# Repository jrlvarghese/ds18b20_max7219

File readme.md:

#DS18B20 is used as a sensor
#MAX7219 used for LED display driver Ic
#Upto 3 digit can be displayed

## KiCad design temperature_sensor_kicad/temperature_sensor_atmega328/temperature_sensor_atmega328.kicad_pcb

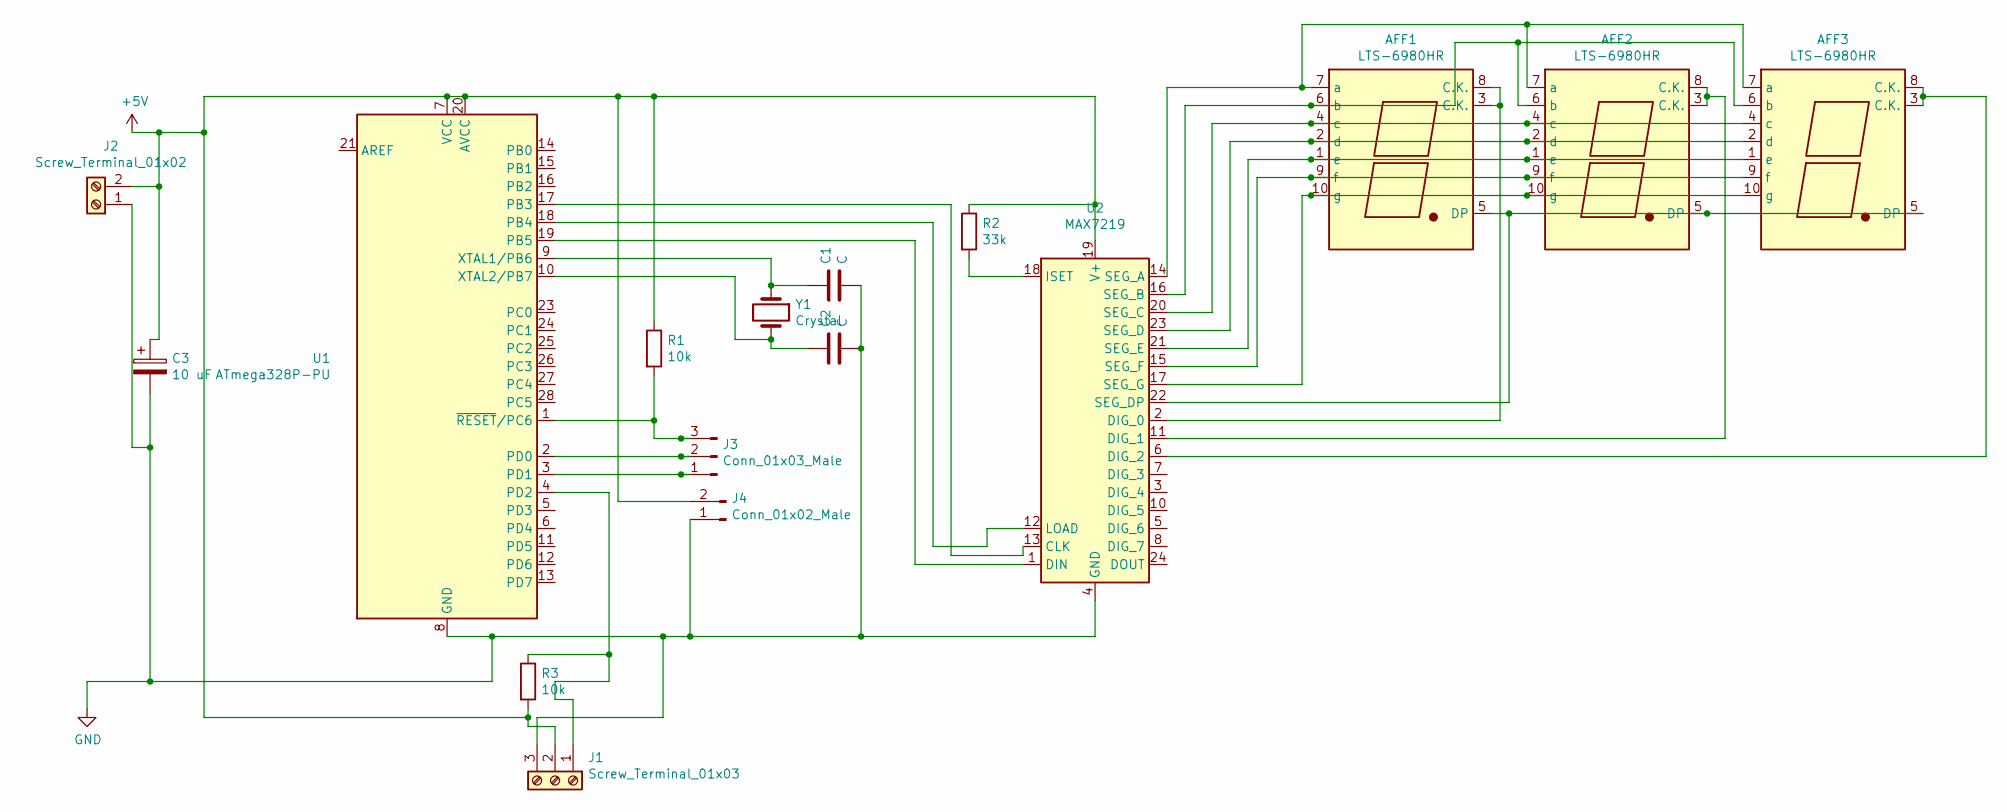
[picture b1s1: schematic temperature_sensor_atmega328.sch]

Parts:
AFF1, AFF2, AFF3: LTS-6980HR; 7SegmentLED_LTS6760_LTS6780
C1, C2: C; C_Disc_D5.0mm_W2.5mm_P5.00mm
C3: 10 uF; CP_Radial_D7.5mm_P2.50mm
J1: Screw_Terminal_01x03; TerminalBlock_bornier-3_P5.08mm
J2: Screw_Terminal_01x02; TerminalBlock_bornier-2_P5.08mm
J3: Conn_01x03_Male; PinHeader_1x03_P2.54mm_Vertical
J4: Conn_01x02_Male; PinHeader_1x02_P2.54mm_Vertical
R1: 10k; R_Axial_DIN0411_L9.9mm_D3.6mm_P15.24mm_Horizontal
R2: 33k; R_Axial_DIN0207_L6.3mm_D2.5mm_P2.54mm_Vertical
R3: 10k; R_Axial_DIN0204_L3.6mm_D1.6mm_P2.54mm_Vertical
U1: ATmega328P-PU; DIP-28_W7.62mm_Socket
U2: MAX7219; DIP-24_W7.62mm
Y1: Crystal; Crystal_HC49-U_Vertical

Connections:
+5V: C3.1, J1.2, J2.2, J4.2, R1.1, R2.1, R3.2, U1.7 (VCC), U1.20 (AVCC), U2.19 (V+)
GND: C1.2, C2.2, C3.2, J1.3, J2.1, J4.1, U1.8 (GND), U1.22 (GND), U2.4 (GND), U2.9 (GND)
unnamed: AFF1.1 (e), AFF2.1 (e), AFF3.1 (e), U2.21 (SEG_E)
unnamed: AFF1.2 (d), AFF2.2 (d), AFF3.2 (d), U2.23 (SEG_D)
unnamed: AFF1.3 (C.K.), AFF1.8 (C.K.), U2.2 (DIG_0)
unnamed: AFF1.4 (c), AFF2.4 (c), AFF3.4 (c), U2.20 (SEG_C)
unnamed: AFF1.5 (DP), AFF2.5 (DP), AFF3.5 (DP), U2.22 (SEG_DP)
unnamed: AFF1.6 (b), AFF2.6 (b), AFF3.6 (b), U2.16 (SEG_B)
unnamed: AFF1.7 (a), AFF2.7 (a), AFF3.7 (a), U2.14 (SEG_A)
unnamed: AFF1.9 (f), AFF2.9 (f), AFF3.9 (f), U2.15 (SEG_F)
unnamed: AFF1.10 (g), AFF2.10 (g), AFF3.10 (g), U2.17 (SEG_G)
unnamed: AFF2.3 (C.K.), AFF2.8 (C.K.), U2.11 (DIG_1)
unnamed: AFF3.3 (C.K.), AFF3.8 (C.K.), U2.6 (DIG_2)
unnamed: C1.1, U1.9 (XTAL1/PB6), Y1.1
unnamed: C2.1, U1.10 (XTAL2/PB7), Y1.2
unnamed: J1.1, R3.1, U1.4 (PD2)
unnamed: J3.1, U1.3 (PD1)
unnamed: J3.2, U1.2 (PD0)
unnamed: J3.3, R1.2, U1.1 (~RESET~/PC6)
unnamed: R2.2, U2.18 (ISET)
unnamed: U1.17 (PB3), U2.13 (CLK)
unnamed: U1.18 (PB4), U2.12 (LOAD)
unnamed: U1.19 (PB5), U2.1 (DIN)

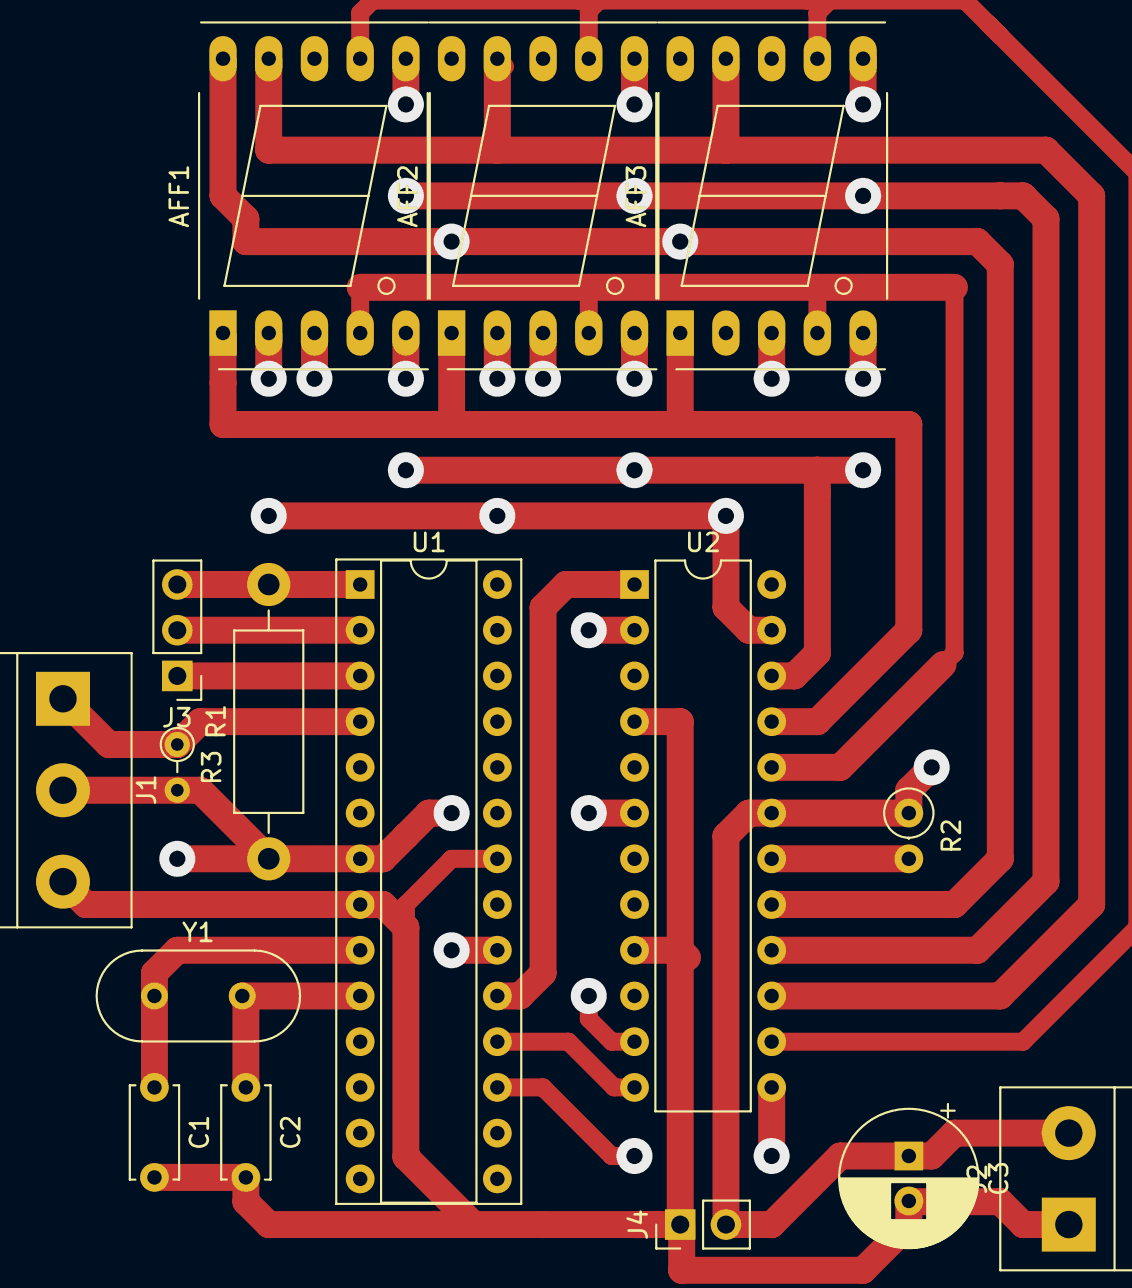
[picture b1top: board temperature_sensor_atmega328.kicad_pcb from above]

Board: 2 copper layers, 16 parts (0 on the bottom side), 23 nets.

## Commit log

2021-02-17 Temperature sensor circuit and code working.
2021-02-17 Add readme.md
